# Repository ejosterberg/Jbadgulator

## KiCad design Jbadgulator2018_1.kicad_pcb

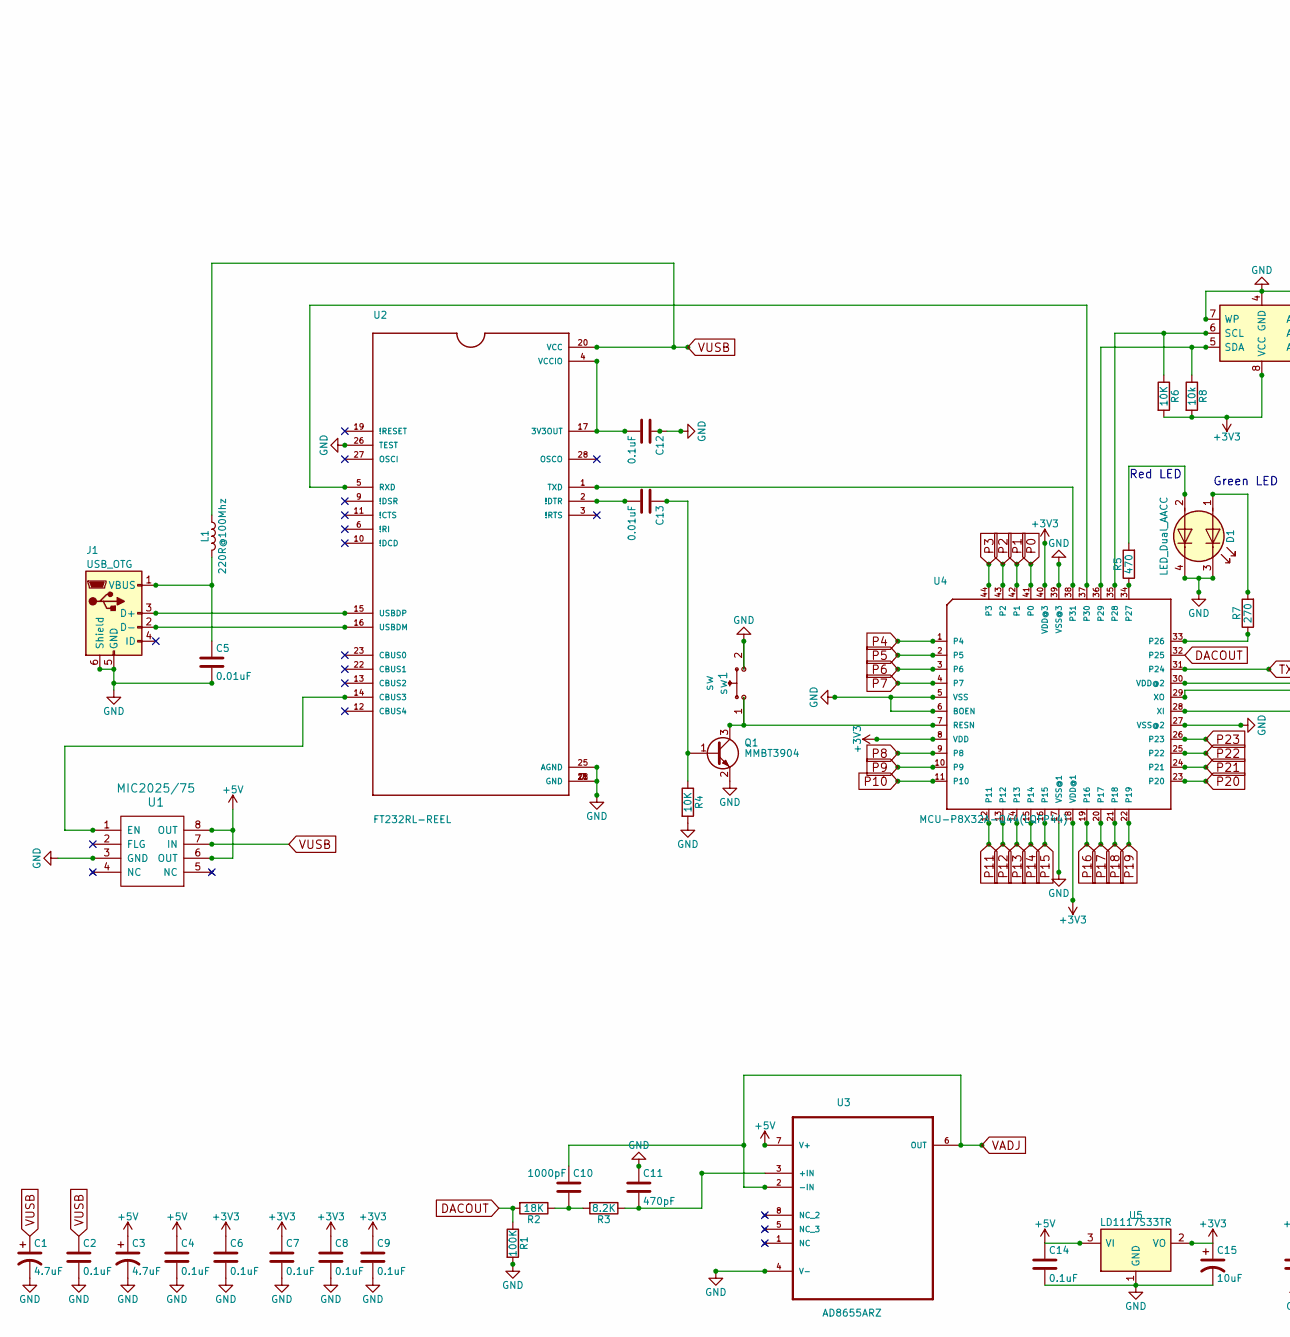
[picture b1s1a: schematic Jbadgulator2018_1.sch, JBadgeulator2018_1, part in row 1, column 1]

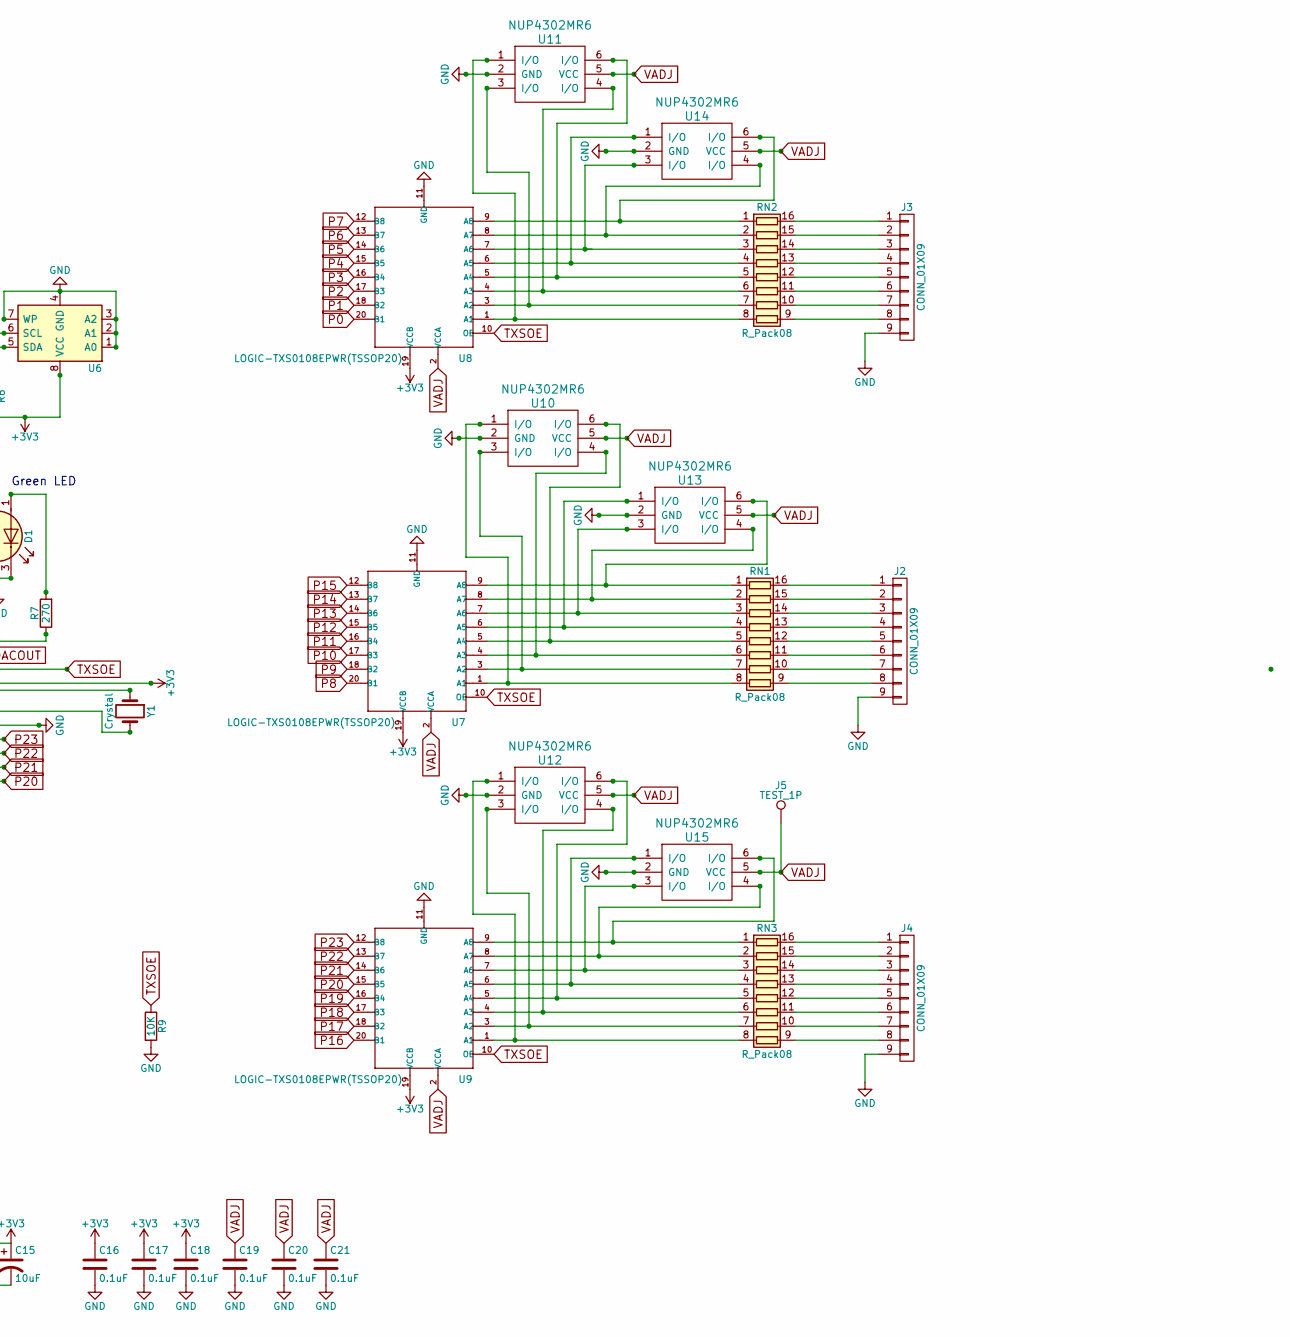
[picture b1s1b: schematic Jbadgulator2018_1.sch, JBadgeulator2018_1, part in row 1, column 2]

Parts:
C1, C3: 4.7uF; C_1206_HandSoldering
C2, C4, C6, C7, C8, C9, C12, C14, C16, C17, C18, C19, C20, C21: 0.1uF; C_1206_HandSoldering
C5, C13: 0.01uF; C_1206_HandSoldering
C10: 1000pF; C_1206_HandSoldering
C11: 470pF; C_1206_HandSoldering
C15: 10uF; C_1206_HandSoldering
D1: LED_Dual_AACC; ChTownDualLED
J1: USB_OTG; USB_Micro-CN
J2, J3, J4: CONN_01X09; Pin_Header_Angled_1x09_Pitch2.54mm
J5: TEST_1P; Measurement_Point_Round-TH_Small
L1: 220R@100Mhz; R_0805
Q1: MMBT3904; TSOT-23_HandSoldering
R1: 100K; R_1206_HandSoldering
R2: 18K; R_1206_HandSoldering
R3: 8.2K; R_1206_HandSoldering
R4, R6, R9: 10K; R_1206_HandSoldering
R5: 470; R_1206_HandSoldering
R7: 270; R_1206_HandSoldering
R8: 10k; R_1206_HandSoldering
RN1, RN2, RN3: R_Pack08; SOIC-16W_5.3x10.2mm_Pitch1.27mm
U1: MIC2025/75; SOIC-8-N
U2: FT232RL-REEL; SSOP-28_5.3x10.2mm_Pitch0.65mm
U3: AD8655ARZ; SOIC127P600X175-8N
U4: MCU-P8X32A-Q44(LQFP44); LQFP-44_10x10mm_Pitch0.8mm
U5: LD1117S33TR; SOT-223-3_TabPin2
U6: 24LC512; SOIC-8_3.9x4.9mm_Pitch1.27mm
U7, U8, U9: LOGIC-TXS0108EPWR(TSSOP20); TSSOP-20_4.4x6.5mm_Pitch0.65mm
U10, U11, U12, U13, U14, U15: NUP4302MR6; TSOP-6_1.65x3.05mm_Pitch0.95mm
Y1: Crystal; Crystal_SMD_HC49-SD
sw1: sw; SW_SPST_B3SL-1002P

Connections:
+3V3: C6.1, C7.1, C8.1, C9.1, C15.1, C16.1, C17.1, C18.1, R6.2, R8.2, U4.8 (VDD), U4.18 (VDD@1), U4.30 (VDD@2), U4.40 (VDD@3), U5.2 (VO), U6.8 (VCC), U7.19 (VCCB), U8.19 (VCCB), U9.19 (VCCB)
+5V: C3.1, C4.1, C14.1, U1.6 (OUT), U1.8 (OUT), U3.7 (V+), U5.3 (VI)
DACOUT: R1.1, R2.2, U4.32 (P25)
GND: C1.2, C2.2, C3.2, C4.2, C5.2, C6.2, C7.2, C8.2, C9.2, C11.1, C12.1, C14.2, C15.2, C16.2, C17.2, C18.2, C19.2, C20.2, C21.2, D1.3 (K1), D1.4 (K2), J1.5 (GND), J1.6 (Shield), J2.9, J3.9, J4.9, Q1.2 (E), R1.2, R4.2, R9.2, U1.3 (GND), U2.7 (GND), U2.18 (GND), U2.21 (GND), U2.25 (AGND), U2.26 (TEST), U3.4 (V-), U4.5 (VSS), U4.6 (BOEN), U4.17 (VSS@1), U4.27 (VSS@2), U4.39 (VSS@3), U5.1 (GND), U6.1 (A0), U6.2 (A1), U6.3 (A2), U6.4 (GND), U6.7 (WP), U7.11 (GND), U8.11 (GND), U9.11 (GND), U10.2 (GND), U11.2 (GND), U12.2 (GND), U13.2 (GND), U14.2 (GND), U15.2 (GND), sw1.2
unnamed: C5.1, J1.1 (VBUS), L1.2
unnamed: C10.2, R2.1, R3.2
unnamed: C11.2, R3.1, U3.3 (+IN)
unnamed: C12.2, U2.4 (VCCIO), U2.17 (3V3OUT)
unnamed: C13.1, Q1.1 (B), R4.1
unnamed: C13.2, U2.2 (!DTR)
unnamed: D1.1 (A1), R7.2
unnamed: D1.2 (A2), R5.2
unnamed: J1.2 (D-), U2.16 (USBDM)
unnamed: J1.3 (D+), U2.15 (USBDP)
unnamed: J2.1, RN1.16 (R1.2)
unnamed: J2.2, RN1.15 (R2.2)
unnamed: J2.3, RN1.14 (R3.2)
unnamed: J2.4, RN1.13 (R4.2)
unnamed: J2.5, RN1.12 (R5.2)
unnamed: J2.6, RN1.11 (R6.2)
unnamed: J2.7, RN1.10 (R7.2)
unnamed: J2.8, RN1.9 (R8.2)
unnamed: J3.1, RN2.16 (R1.2)
unnamed: J3.2, RN2.15 (R2.2)
unnamed: J3.3, RN2.14 (R3.2)
unnamed: J3.4, RN2.13 (R4.2)
unnamed: J3.5, RN2.12 (R5.2)
unnamed: J3.6, RN2.11 (R6.2)
unnamed: J3.7, RN2.10 (R7.2)
unnamed: J3.8, RN2.9 (R8.2)
unnamed: J4.1, RN3.16 (R1.2)
unnamed: J4.2, RN3.15 (R2.2)
unnamed: J4.3, RN3.14 (R3.2)
unnamed: J4.4, RN3.13 (R4.2)
unnamed: J4.5, RN3.12 (R5.2)
unnamed: J4.6, RN3.11 (R6.2)
unnamed: J4.7, RN3.10 (R7.2)
unnamed: J4.8, RN3.9 (R8.2)
unnamed: Q1.3 (C), U4.7 (RESN), sw1.1
unnamed: R5.1, U4.34 (P27)
unnamed: R6.1, U4.35 (P28), U6.6 (SCL)
unnamed: R7.1, U4.33 (P26)
unnamed: R8.1, U4.36 (P29), U6.5 (SDA)
unnamed: RN1.1 (R1.1), U7.9 (A8), U13.6 (I/O)
unnamed: RN1.2 (R2.1), U7.8 (A7), U13.4 (I/O)
unnamed: RN1.3 (R3.1), U7.7 (A6), U13.3 (I/O)
unnamed: RN1.4 (R4.1), U7.6 (A5), U13.1 (I/O)
unnamed: RN1.5 (R5.1), U7.5 (A4), U10.6 (I/O)
unnamed: RN1.6 (R6.1), U7.4 (A3), U10.4 (I/O)
unnamed: RN1.7 (R7.1), U7.3 (A2), U10.3 (I/O)
unnamed: RN1.8 (R8.1), U7.1 (A1), U10.1 (I/O)
unnamed: RN2.1 (R1.1), U8.9 (A8), U14.6 (I/O)
unnamed: RN2.2 (R2.1), U8.8 (A7), U14.4 (I/O)
unnamed: RN2.3 (R3.1), U8.7 (A6), U14.3 (I/O)
unnamed: RN2.4 (R4.1), U8.6 (A5), U14.1 (I/O)
unnamed: RN2.5 (R5.1), U8.5 (A4), U11.6 (I/O)
unnamed: RN2.6 (R6.1), U8.4 (A3), U11.4 (I/O)
unnamed: RN2.7 (R7.1), U8.3 (A2), U11.3 (I/O)
unnamed: RN2.8 (R8.1), U8.1 (A1), U11.1 (I/O)
unnamed: RN3.1 (R1.1), U9.9 (A8), U15.6 (I/O)
unnamed: RN3.2 (R2.1), U9.8 (A7), U15.4 (I/O)
unnamed: RN3.3 (R3.1), U9.7 (A6), U15.3 (I/O)
unnamed: RN3.4 (R4.1), U9.6 (A5), U15.1 (I/O)
unnamed: RN3.5 (R5.1), U9.5 (A4), U12.6 (I/O)
unnamed: RN3.6 (R6.1), U9.4 (A3), U12.4 (I/O)
unnamed: RN3.7 (R7.1), U9.3 (A2), U12.3 (I/O)
unnamed: RN3.8 (R8.1), U9.1 (A1), U12.1 (I/O)
unnamed: U1.1 (EN), U2.14 (CBUS3)
unnamed: U2.1 (TXD), U4.38 (P31)
unnamed: U2.5 (RXD), U4.37 (P30)
unnamed: U4.28 (XI), Y1.2
unnamed: U4.29 (XO), Y1.1
P0: U4.41 (P0), U8.20 (B1)
P1: U4.42 (P1), U8.18 (B2)
P2: U4.43 (P2), U8.17 (B3)
P3: U4.44 (P3), U8.16 (B4)
P4: U4.1 (P4), U8.15 (B5)
P5: U4.2 (P5), U8.14 (B6)
P6: U4.3 (P6), U8.13 (B7)
P7: U4.4 (P7), U8.12 (B8)
P8: U4.9 (P8), U7.20 (B1)
P9: U4.10 (P9), U7.18 (B2)
P10: U4.11 (P10), U7.17 (B3)
P11: U4.12 (P11), U7.16 (B4)
P12: U4.13 (P12), U7.15 (B5)
P13: U4.14 (P13), U7.14 (B6)
P14: U4.15 (P14), U7.13 (B7)
P15: U4.16 (P15), U7.12 (B8)
P16: U4.19 (P16), U9.20 (B1)
P17: U4.20 (P17), U9.18 (B2)
P18: U4.21 (P18), U9.17 (B3)
P19: U4.22 (P19), U9.16 (B4)
P20: U4.23 (P20), U9.15 (B5)
P21: U4.24 (P21), U9.14 (B6)
P22: U4.25 (P22), U9.13 (B7)
P23: U4.26 (P23), U9.12 (B8)
TXSOE: R9.1, U4.31 (P24), U7.10 (OE), U8.10 (OE), U9.10 (OE)
VADJ: C10.1, C19.1, C20.1, C21.1, J5.1, U3.2 (-IN), U3.6 (OUT), U7.2 (VCCA), U8.2 (VCCA), U9.2 (VCCA), U10.5 (VCC), U11.5 (VCC), U12.5 (VCC), U13.5 (VCC), U14.5 (VCC), U15.5 (VCC); also elsewhere on the board
VUSB: C1.1, C2.1, L1.1, U1.7 (IN), U2.20 (VCC)

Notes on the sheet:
Red LED
Green LED

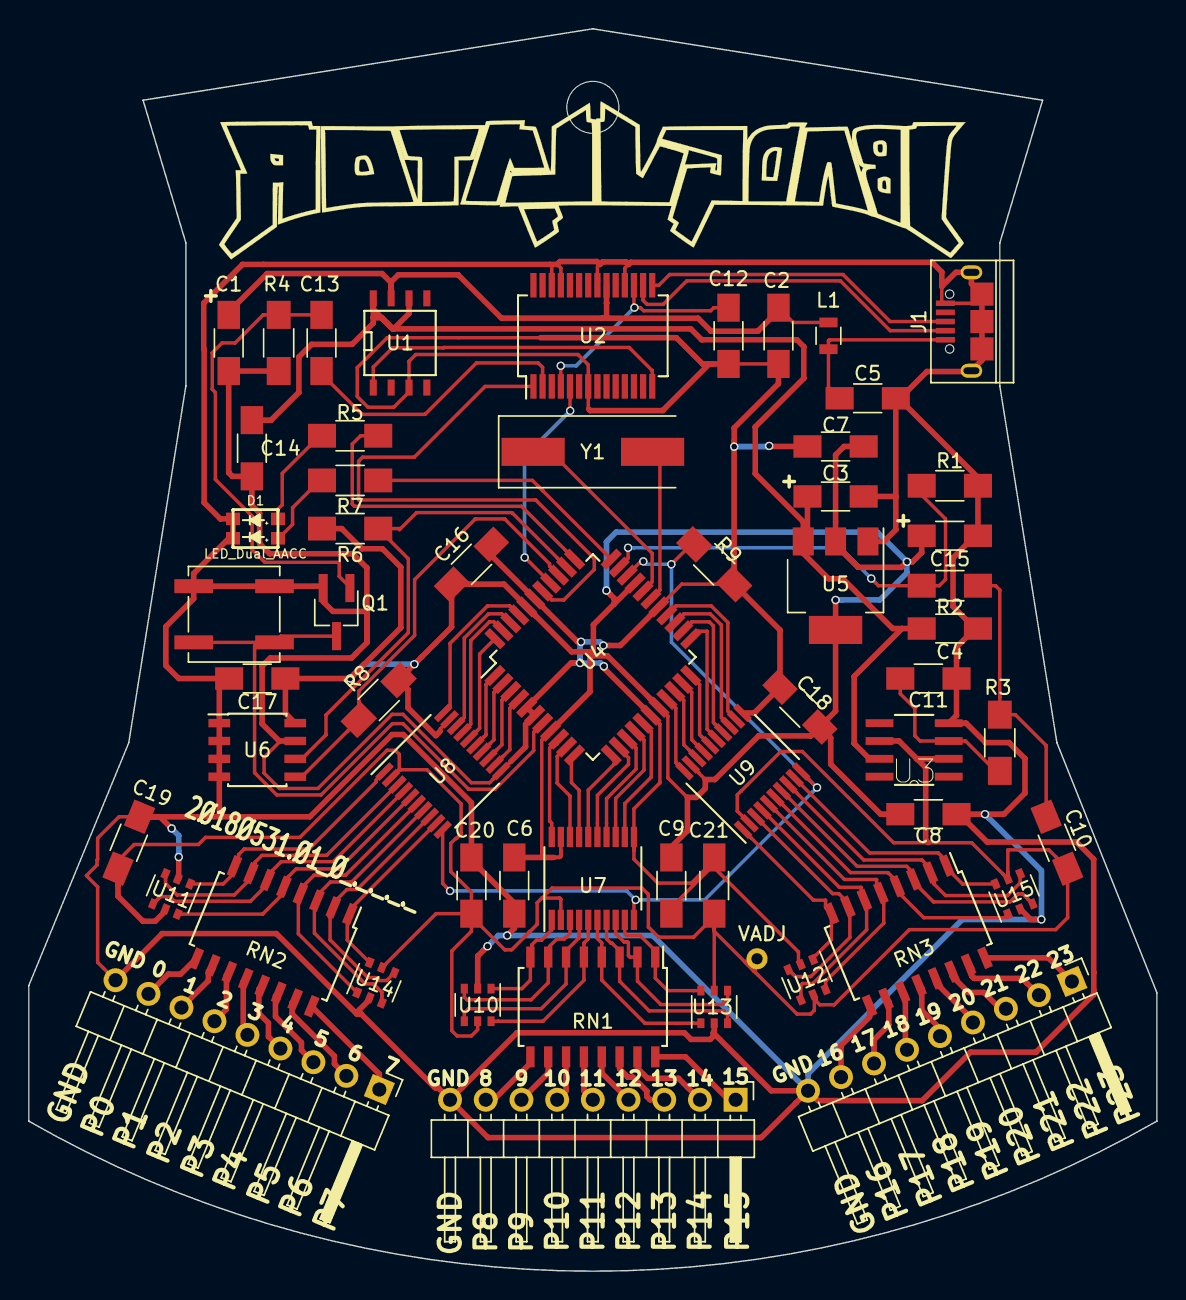
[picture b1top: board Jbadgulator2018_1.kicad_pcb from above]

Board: 2 copper layers, 80.3 x 88.4 mm, 58 parts (0 on the bottom side), 99 nets.

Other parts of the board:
VADJ: TEST_1P; Measurement_Point_Round-TH_Small

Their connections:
VADJ: VADJ.1; also elsewhere on the board

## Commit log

2018-08-22 Initial commit - DefCon26 Jbadgulator jtagulator clone

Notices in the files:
Jbadgulator2018_1.kicad_pcb:
© 2013 - (CC BY-SA 3.0)
